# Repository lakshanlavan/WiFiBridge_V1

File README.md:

# 📶 WiFiBridge V1

### 🔧 Project Overview

**WiFiBridge V1** is a compact, battery-powered Wi-Fi bridge designed by **Lakshan Lavan**.  
It leverages the **WT32-ETH01 WiFi module** and features power-efficient circuitry, UART-based communication, and robust modularity for IoT and automation tasks.

---

## 🧩 Key Features

- ✅ WT32-ETH01 (ESP32-based WiFi + Ethernet module)
- 🔋 18650 battery integration for mobile applications
- 💡 LED indicators for:
  - Power status
  - WiFi connectivity
  - Battery charging and full charge
- 📤 Pick-and-place ready with `.csv` top position file
- 🪛 Custom KiCad footprints for modular components
- 🧠 Designed for compact routing and easy assembly

---

## 🏭 Fabrication Notes

- ✅ No Gerbers are published.  
  You can open the `.kicad_pcb` file in [KiCad](https://kicad.org/) to generate fabrication files if needed.
- Designed with **JLCPCB component compatibility** in mind.
- Supports **SMD assembly** using `.csv` pick-and-place file.

---

## ⚠️ Disclaimer

This project is open-source and provided as-is. Modify, improve, or integrate it freely into your own systems.

---

## 👤 Author

**Lakshan Lavan**  
Embedded Systems | Robotics | PCB Design  
[LinkedIn](https://www.linkedin.com/in/lakshan29) | [Email](mailto:lakshanlavan29@gmail.com)

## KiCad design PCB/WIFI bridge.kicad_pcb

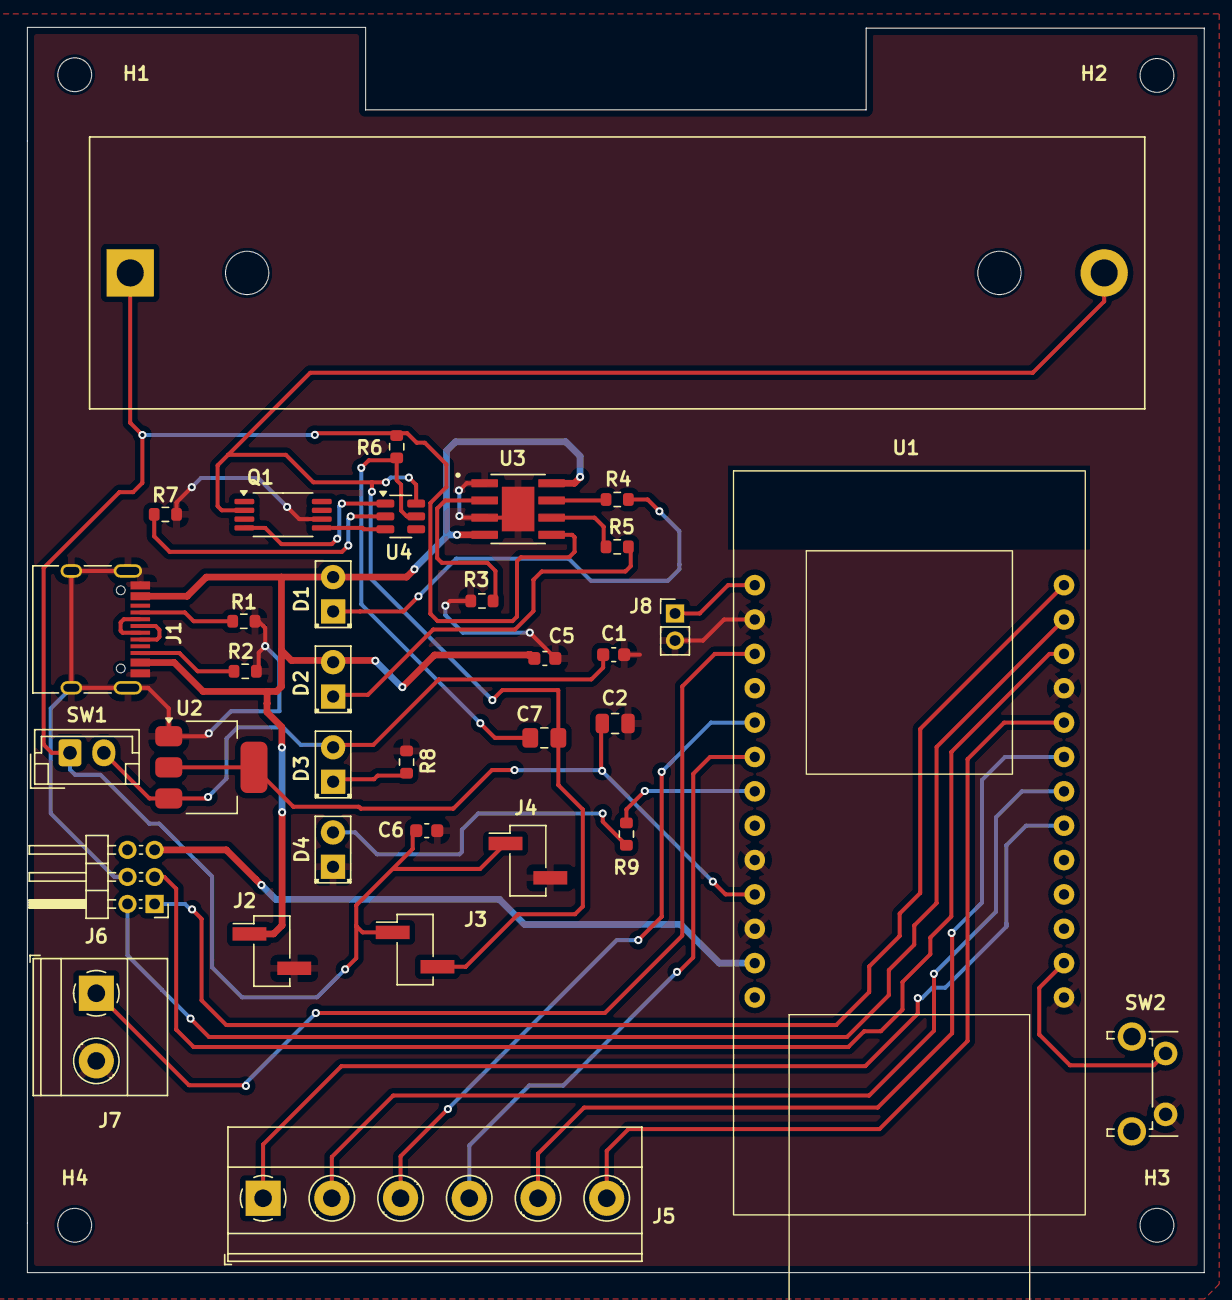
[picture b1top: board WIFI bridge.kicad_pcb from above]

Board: 2 copper layers, 87.0 x 92.0 mm, 38 parts (0 on the bottom side), 35 nets.

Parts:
BT1: Battery_Cell; BatteryHolder_MPD_BH-18650-PC2
C1, C6: 10u; C_0603_1608Metric
C2: 22u; C_0805_2012Metric
C5: 100n; C_0603_1608Metric
C7: 100n; C_0805_2012Metric_Pad1.18x1.45mm_HandSolder
D1, D2, D3, D4: LED; LED_D2.0mm_W4.8mm_H2.5mm_FlatTop
H1, H2, H3, H4: MountingHole; MountingHole_2.5mm
J1: USB_C_Receptacle_USB2.0_16P; USB_C_Receptacle_HRO_TYPE-C-31-M-12
J2: +-; PinHeader_1x02_P2.54mm_Vertical_SMD_Pin1Left
J3: 1B+2B-; PinHeader_1x02_P2.54mm_Vertical_SMD_Pin1Left
J4: 1OUT+2OUT-; PinHeader_1x02_P2.54mm_Vertical_SMD_Pin1Left
J5: Screw_Terminal_01x06; TerminalBlock_Phoenix_MKDS-1,5-6-5.08_1x06_P5.08mm_Horizont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
J6: Conn_02x03_Counter_Clockwise; PinHeader_2x03_P2.00mm_Horizontal
J7: Screw_Terminal_01x02; TerminalBlock_Phoenix_MKDS-1,5-2_1x02_P5.00mm_Horizontal
J8: Conn_01x02_Pin; PinHeader_1x02_P2.00mm_Vertical
Q1: FS8205A; TSSOP-8_4.4x3mm_P0.65mm
R1, R2: 5k1; R_0603_1608Metric
R3: 1k2; R_0603_1608Metric
R4, R5, R7: 1k; R_0603_1608Metric
R6: 100; R_0603_1608Metric
R8: 680; R_0603_1608Metric
R9: 220; R_0603_1608Metric
SW1: SW_SPST; JST_EH_B2B-EH-A_1x02_P2.50mm_Vertical
SW2: SW_Push; SW_Tactile_SPST_Angled_PTS645Vx58-2LFS
U1: WT32-ETH01
U2: AMS1117-3.3; SOT-223-3_TabPin2
U3: TP4056; SOP127P600X175-9N
U4: DW01A; SOT-23-6

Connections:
5V: J6.5, U1.12 (5V)
+3.3V: C2.1, U1.10 (3.3V), U2.2 (VO)
+5V: C5.1, D1.2 (A), D2.2 (A), J1.A4 (VBUS), J1.A9 (VBUS), J1.B4 (VBUS), J1.B9 (VBUS), J2.1, U3.4 (VCC), U3.8 (CE)
/3.3V: J7.1, U1.3 (3.3V)
/BAT: BT1.1 (+), C6.1, J3.1, J4.1, R6.2, SW1.1 (A), U3.5 (BAT)
/BOUT: C1.1, D3.2 (A), SW1.2 (B), U2.3 (VI)
/CHRG: R4.1, U3.7 (~CHRG)
/IO0: J6.3, U1.24 (IO0/PRG_LOW/ETH_CLK)
/IO14: J5.1, U1.19 (IO14/ADC2_CH6/TCH6)
/IO15: J5.2, U1.20 (IO15/ADC2_CH3/TCH3)
/IO32: J5.3, U1.5 (IO32/ADC1_CH4/TCH9)
/IO33: J5.4, U1.6 (IO33/ADC1_CH5/TCH8)
/IO36: J5.5, U1.21 (IO36/ADC1_CH0/INPUT_ONLY)
/IO39: J5.6, U1.22 (IO39/ADC1_CH3/INPUT_ONLY)
/RX: J6.2, U1.25 (IO3/PRG_RX)
/STDBY: R5.1, U3.6 (~STDBY)
/TX: J6.1, U1.26 (IO1/PRG_TX)
/dw_gnd: BT1.2 (-), C7.2, J3.2, Q1.2, U4.6 (GND)
/dw_vcc: C7.1, R6.1, U4.5 (VCC)
ENB: J8.1, U1.1 (CLK_EN)
GND: C1.2, C2.2, C5.2, C6.2, D4.1 (K), J1.A1 (GND), J1.A12 (GND), J1.B1 (GND), J1.B12 (GND), J1.S1 (SHIELD), J2.2, J4.2, J6.4, J7.2, J8.2, Q1.6, R1.2, R2.2, R3.1, R7.2, R8.1, SW2.2, U1.2 (GND), U1.9 (GND), U1.11 (GND), U1.14 (GND), U1.23 (GND), U2.1 (GND), U3.1 (TEMP), U3.3 (GND), U3.9 (EP)
IPSET: SW2.1, U1.15 (IO2/ADC2_CH2/TCH2/PRG_FLOAT_OR_GND)
unnamed: D1.1 (K), R4.2
unnamed: D2.1 (K), R5.2
unnamed: D3.1 (K), R8.2
unnamed: D4.2 (A), R9.1
unnamed: J1.A5 (CC1), R1.1
unnamed: J1.B5 (CC2), R2.1
unnamed: J1.A6 (D+), J1.B6 (D+)
unnamed: J1.A7 (D-), J1.B7 (D-)
unnamed: R9.2, U1.7 (IO5/BOOT_FLOAT)
unnamed: R3.2, U3.2 (PROG)
unnamed: R7.1, U4.2 (CS)
unnamed: Q1.5, U4.3 (OC)
unnamed: Q1.4, U4.1 (OD)

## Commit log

2025-07-28 Rename README_WiFiBridge_V1.md to README.md
2025-07-28 Rename LICENSE_WiFiBridge_V1.txt to LICENSE
